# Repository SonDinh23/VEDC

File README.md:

# VEDC.dev

<div align="center">

<sub>
  Vedc v0.1 Front Top product (left), Front Bottom product (right)
</sub>

<sub>
  Vedc v0.1 Back Top product (left), Back Bottom product (right)
</sub>
</div>

## Table of contents

- [About](#about)
- [Platform snapshot](#platform-snapshot)
- [Features](#features)
  - [Hardware](#hardware)
  - [Firmware](#firmware)
  - [Software](#software)
- [Environment & build](#environment--build)
- [Writing apps for the Application Manager](#writing-apps-for-the-application-manager)
- [Licence GPL-3.0](#licence-gpl-30)
- [Thanks](#thanks)

## About

VEDC is a wearable biomedical reference design that blends EMG, ECG, and PPG sensing in a developer-friendly package. The hardware stack is fully captured in KiCad, the firmware targets ESP32-PICO-V3-02 via PlatformIO, and all production assets live in this repo so you can reproduce the build or remix it for your own research.

## Platform snapshot

| Item | Detail |
| --- | --- |
| MCU | ESP32-PICO-V3-02 (dual-core Xtensa®, Wi-Fi + BLE, 8 MB flash, 2 MB PSRAM) |
| Sensors | EMG analog front-end, ECG (AD8232), PPG module, 6-axis IMU, magnetometer |
| Connectivity | Wi-Fi 2.4 GHz, Bluetooth v4.2, USB-C (CP2102N), TWAI®/CAN-ready |
| Power | Single-cell Li-Ion + TP4056 charger + XC6220 LDO + smart power-path on MainPCB |
| Target use | Physiology research, medical wearables prototyping, advanced hobby builds |

### Core silicon & companion parts

- ESP32-PICO-V3-02 ([datasheet](https://documentation.espressif.com/esp32-pico_series_datasheet_en.pdf)) with Xtensa® LX6 up to 240 MHz, Wi-Fi/BLE, Ethernet MAC and TWAI®.
- Torex [XC6220B331MR-G](https://www.farnell.com/datasheets/2012852.pdf) 1 A, 3.3 V low-noise LDO for the digital rail.
- Silicon Labs [CP2102N-A02-GQFN28](https://www.silabs.com/documents/public/data-sheets/cp2102n-datasheet.pdf) USB-to-UART bridge for flashing, logging and live telemetry.
- Worldsemi [WS2812B-2020](https://www.mouser.com/pdfDocs/WS2812B-2020_V10_EN_181106150240761.pdf) RGB indicator, Murata [PKMCS0909E4000-R1](https://pim.murata.com/en-us/pim/details/?partNum=PKMCS0909E4000-R1) piezo buzzer, Microchip [MCP3204](https://ww1.microchip.com/downloads/en/devicedoc/21298e.pdf) SPI ADC.
- ST [LSM6DSL](https://www.st.com/resource/en/datasheet/lsm6dsl.pdf) IMU + [LIS3MDL](https://www.st.com/resource/en/datasheet/lis3mdl.pdf) magnetometer for motion/orientation tracking.
- Analog Devices [AD8232](https://www.analog.com/media/en/technical-documentation/data-sheets/ad8232.pdf) ECG AFE and a custom EMG front-end for bio-signal capture.
- TPASIC [TP4056](https://datasheet.lcsc.com/lcsc/1809261820_TOPPOWER-Nanjing-Extension-Microelectronics-TP4056-42-ESOP8_C16581.pdf) charger IC for USB-powered Li-Ion management.

## Features

### Hardware

- Three KiCad projects: EMGSensor, MainPCB, and PPG_V1.0. Each board section includes schematics, PCB layout, manufacturing outputs, notes, and galleries.
- Design focus on low-noise analog front-ends, modular interconnects, and easy probing during validation.
- Production-ready assets: BOM, pick-and-place, netlist, and positional data are stored under every `production/` folder.

[Browse board documentation →](hardware/README.md)

### Firmware

- ESP-IDF/PlatformIO stack targeting ESP32-PICO-V3-02 with FreeRTOS scheduling, NimBLE-based BLE services, USB-UART telemetry, and low-power modes.
- Sensor pipelines for EMG/ECG/PPG including digital filtering, adaptive baseline tracking, and event triggers for motion artifacts.
- Modular drivers housed under `firmware/Embedded/lib/` plus an application layer that streams metrics to BLE characteristics or logs via UART.
- Includes board bring-up helpers (rail monitors, sensor self-tests) and a configurable command shell.

[Read the full firmware guide →](firmware/README.md)

### Software

- Companion tooling (desktop/mobile) is planned to visualize BLE data streams, annotate sessions, and push OTA payloads.
- Current repo includes assets and API constraints so third parties can prototype dashboards or research tools ahead of the official release.
- Planned features: live waveform view, biomarker extraction scripts, and CSV export for MATLAB/Python workflows.

Have tooling to share? Open an issue so we can link it here.

## Environment & build

### Requirements

- VS Code with the PlatformIO IDE extension (or PlatformIO Core CLI).
- Python 3.10+ (PlatformIO manages the toolchain, but Python is still required).
- KiCad 7+ if you plan to edit the hardware.
- Git LFS for large media assets (images/live captures).

### Quick start

1. Clone the repo: `git clone https://github.com/SonDinh23/VEDC.git && cd VEDC`.
2. Open VS Code -> `firmware/` folder -> PlatformIO will auto-configure the environment.
3. Build: `pio run` (or the PlatformIO Build button).
4. Flash: connect the board over USB-C, then `pio run -t upload`.
5. Monitor logs: `pio device monitor` for UART output, or use the BLE explorer of your choice to view live characteristics.
6. Hardware tweaks: jump into `hardware/README.md` to pick the board you want to fabricate or review.

## Writing apps for the Application Manager

- The Application Manager exposes hooks for real-time sensing apps (recording, feedback) and offline routines (log replay, calibration).
- Apps are plain C++ modules that register tasks, BLE endpoints, and menu entries; use the existing patterns under `firmware/Embedded/src/` and supporting libraries in `firmware/Embedded/lib/` as templates.
- Keep apps lightweight: offload heavy analytics to the companion software via BLE or UART streaming.
- Submit a PR or discussion thread before merging new app types so we can document protocol additions for users.

## Licence GPL-3.0

This project is licensed under the GNU GPLv3.  
Compared to permissive licences like MIT, GPLv3 requires that if you modify this code and distribute your version (including in commercial products), you must also release your changes under the same GPLv3 licence and provide the corresponding source code.  

This way, everyone can benefit from improvements built on top of this project.  
If this licence causes issues for your intended use, feel free to contact me – I’m open to discussing alternatives.

## Thanks

Huge thanks to the open-source communities behind ESP-IDF, PlatformIO, KiCad, and the component vendors whose public documentation made reverse-engineering painless. Additional appreciation goes to early testers who provided waveform captures and enclosure feedback. Reach out if you want to be listed here or contribute design critiques.

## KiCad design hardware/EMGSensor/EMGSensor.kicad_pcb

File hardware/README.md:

# 🔧 Hardware Reference

Reference hub for every PCB in the VEDC stack. Each section collects the essential narrative (what the board does), quick specs, manufacturing artifacts, bring-up notes and a gallery that matches the files committed to this repo.

## 📌 At-a-glance

| Board | Functional role | Primary interfaces | Manufacturing kit |
| --- | --- | --- | --- |
| [EMGSensor](#emgsensor) | Surface EMG analog front-end with selectable filtering | Differential electrodes, analog output to MainPCB/ADC | `EMGSensor/*.kicad_*`, `EMGSensor/production/` |
| [MainPCB](#mainpcb) | System backplane: power, MCU, sensor connectors & user IO | USB-C, SPI, I2C, GPIO, battery charger, programming header | `MainPCB/*.kicad_*`, `MainPCB/production/` |
| [PPG_V1.0](#ppg_v10) | Optical heart-rate/SpO2 module (LED driver + TIA) | LED drive, photodiode TIA, analog output to MainPCB | `PPG_V1.0/*.kicad_*`, `PPG_V1.0/production/` |

---

## 🧠 EMGSensor

### Highlights
- Low-noise EMG front-end with band-pass filtering and input protection.
- Differential electrode inputs converted to a conditioned analog output for the main MCU/ADC.
- Designed to keep the analog ground plane quiet and isolated from digital switching noise.

### Quick specs

| Parameter | Detail |
| --- | --- |
| Signal type | Differential surface EMG |
| Input range | Microvolt → millivolt (depends on electrode placement) |
| Bandwidth | Application-configurable band-pass |
| Output | Analog to `MainPCB` or external ADC |

### Manufacturing files
- `EMGSensor/EMGSensor.kicad_sch`
- `EMGSensor/EMGSensor.kicad_pcb`
- `EMGSensor/production/` (BOM, placements, netlist, positions)

### Build & test checklist
- Keep electrode traces short/shielded and preserve the analog ground island.
- Verify input protection and supply rails before connecting electrodes to humans.
- Adjust filter corners so they align with sampling rate and targeted muscle group.

### Gallery

<table>
  <tr>
    <td align="center"><br><small>Top — module overview</small></td>
    <td align="center"><br><small>Top — amplifier/filter</small></td>
    <td align="center"><br><small>Top — connectors</small></td>
  </tr>
  <tr>
    <td align="center"><br><small>Bottom — solder side</small></td>
    <td align="center"><br><small>Bottom — ground pours</small></td>
    <td align="center"><br><small>Bottom — component placement</small></td>
  </tr>
</table>

---

## 🧭 MainPCB

### Highlights
- Primary compute board with ESP32 module, battery charging/power-path management and sensor interconnects.
- Hosts debug/programming headers, USB-UART bridge, IMU/ADC expansion headers and NeoPixel/buzzer drivers.
- Provides regulated rails (3V3 etc.) and mounting keep-outs for future enclosures.

### Quick specs

| Parameter | Detail |
| --- | --- |
| Core function | Power distribution + embedded processing |
| Key rails | Battery, charger IC, 3V3 LDO, load switches |
| Interfaces | USB/serial, SPI, I2C, ADC, GPIO, programming header |

### Manufacturing files
- `MainPCB/MainPCB.kicad_sch`
- `MainPCB/MainPCB.kicad_pcb`
- `MainPCB/production/` (BOM, placements, netlist, positions)

### Build & test checklist
- Cross-check BOM vs placement before assembly to avoid variant mix-ups.
- Validate mechanical clearances/keep-outs when fitting into an enclosure.
- Probe test points for each rail during bring-up; confirm charger and LDO thermals.

### Gallery

<table>
  <tr>
    <td align="center"><br><small>Top — overview</small></td>
    <td align="center"><br><small>Top — MCU & IO</small></td>
    <td align="center"><br><small>Top — power subsystem</small></td>
  </tr>
  <tr>
    <td align="center"><br><small>Bottom — solder side</small></td>
    <td align="center"><br><small>Bottom — pours & routing</small></td>
    <td align="center"><br><small>Bottom — placement</small></td>
  </tr>
</table>

---

## 💡 PPG_V1.0

### Highlights
- Dual-LED photoplethysmography front-end with transimpedance amplifier.
- Layout keeps LED/photodiode path compact to reduce crosstalk and improve tissue coupling.
- Analog output routes directly to MainPCB analog inputs or an external ADC.

### Quick specs

| Parameter | Detail |
| --- | --- |
| Role | Optical heart-rate / blood-volume sensing |
| Key blocks | LED driver, photodetector + TIA, post-filtering |
| Output | Analog to `MainPCB` / ADC |

### Manufacturing files
- `PPG_V1.0/PPG_V1.0.kicad_sch`
- `PPG_V1.0/PPG_V1.0.kicad_pcb`
- `PPG_V1.0/production/` (BOM, placements, netlist, positions)

### Build & test checklist
- Align LEDs and photodiode carefully; even small misalignments affect signal quality.
- Tune LED current and TIA feedback for the target SNR vs power budget.
- Shield the sensor head from ambient light during characterization.

### Gallery

<table>
  <tr>
    <td align="center"><br><small>Top — overview</small></td>
    <td align="center"><br><small>Top — LED/receiver zone</small></td>
  </tr>
  <tr>
    <td align="center"><br><small>Bottom — solder side</small></td>
    <td align="center"><br><small>Bottom — placement view</small></td>
  </tr>
</table>

---

## 🖼️ Image & path guidance

- Use forward slashes `/` in Markdown image paths; all current links are relative to this README.
- Example snippet: ``.
- GitHub renders images only after the corresponding PNG/SVG files are committed and pushed.
- Need a different layout (per-board README, thumbnail sizes, PDF gallery)? Let me know and I can spin up that structure quickly.

---

_Last refreshed: see git history for author/date of the latest board update._

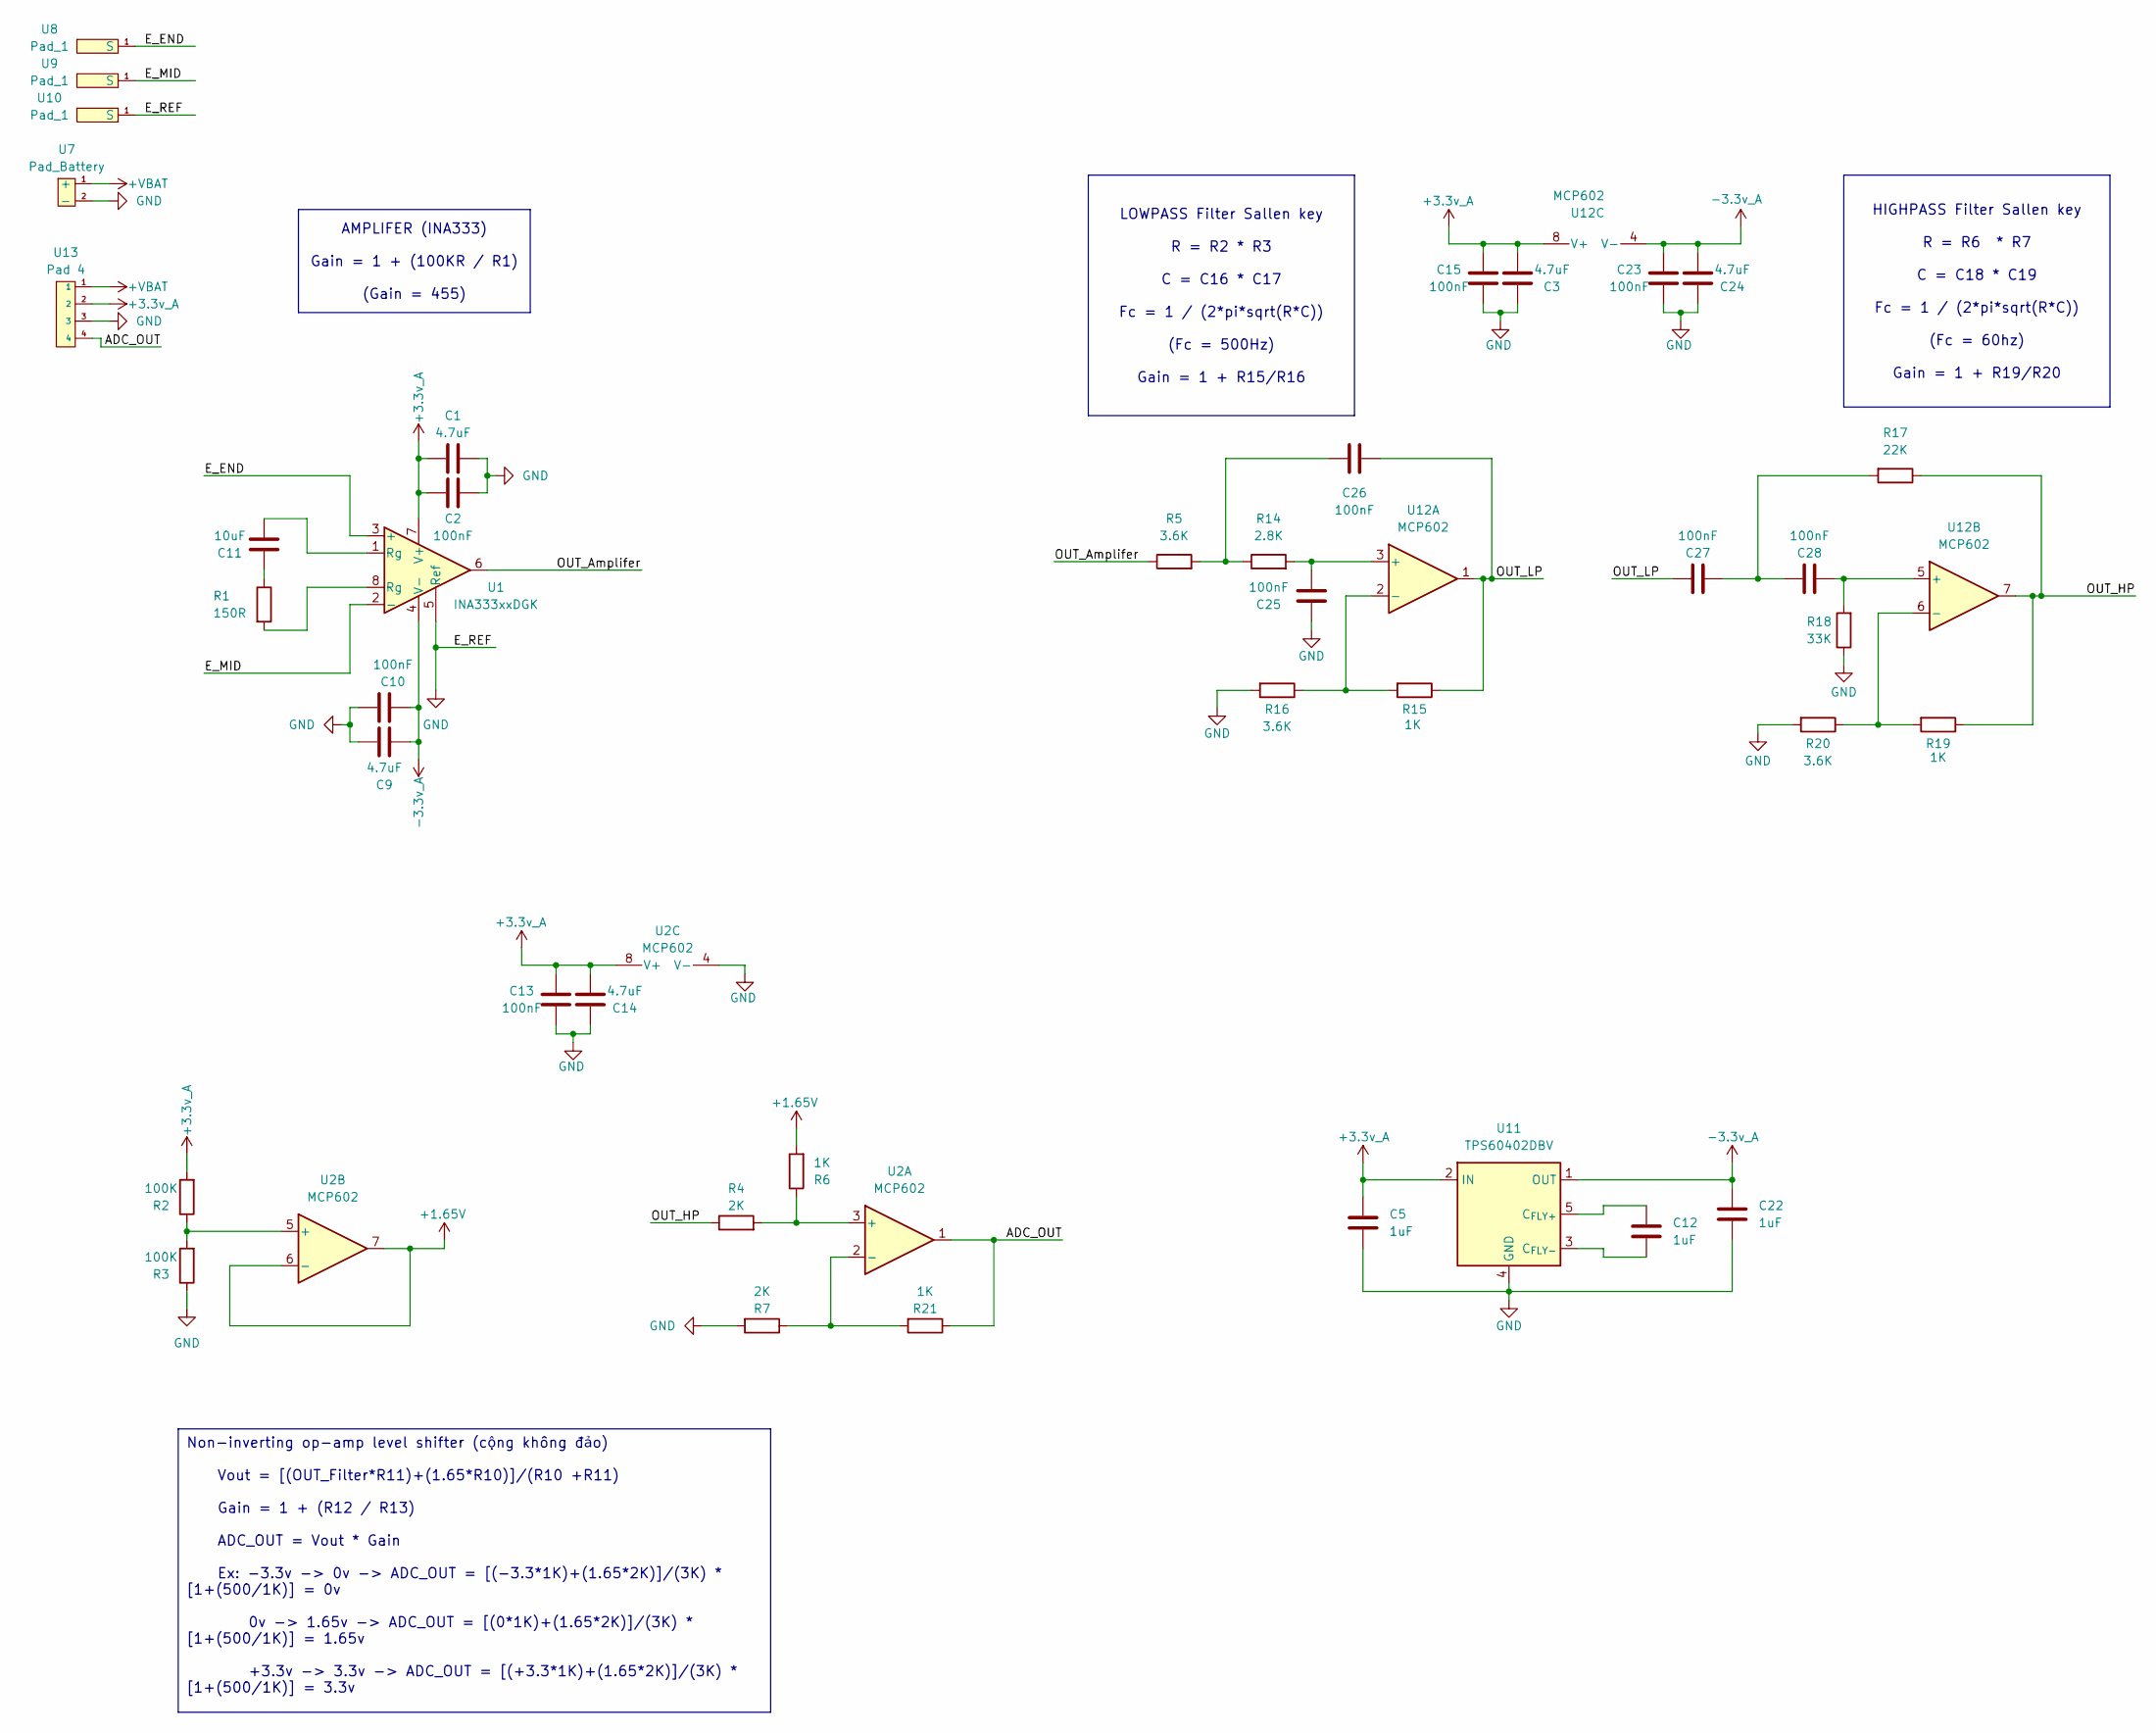
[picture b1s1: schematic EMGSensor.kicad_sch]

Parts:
C1, C3, C9, C14, C24: 4.7uF; C_0402_1005Metric
C2, C10, C13, C15, C23, C25, C26, C27, C28: 100nF; C_0402_1005Metric
C5, C12, C22: 1uF; C_0402_1005Metric
C11: 10uF; C_0603_1608Metric
R1: 150R; R_0402_1005Metric
R2, R3: 100K; R_0402_1005Metric
R4, R7: 2K; R_0402_1005Metric
R5, R16, R20: 3.6K; R_0402_1005Metric
R6, R15, R19, R21: 1K; R_0402_1005Metric
R14: 2.8K; R_0402_1005Metric
R17: 22K; R_0402_1005Metric
R18: 33K; R_0402_1005Metric
U1: INA333xxDGK; VSSOP-8_3x3mm_P0.65mm
U2, U12: MCP602; SOIC-8_3.9x4.9mm_P1.27mm
U7: Pad_Battery; Pad Battery
U8, U9, U10: Pad_1; Pad 1
U11: TPS60402DBV; SOT-23-5
U13: Pad 4

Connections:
+1.65V: R6.2, U2.6 (-), U2.7
+3.3v_A: C1.1, C2.1, C3.1, C5.1, C13.1, C14.1, C15.1, R2.2, U1.7 (V+), U2.8 (V+), U11.2 (IN), U12.8 (V+), U13.2
+VBAT: U7.1 (+), U13.1
-3.3v_A: C9.1, C10.1, C22.1, C23.1, C24.1, U1.4 (V-), U11.1 (OUT), U12.4 (V-)
/ADC_OUT: R21.1, U2.1, U13.4
/E_END: U1.3 (+), U8.1
/E_MID: U1.2 (-), U9.1
/OUT_Amplifer: R5.1, U1.6
/OUT_HP: R4.1, R17.1, R19.1, U12.7
/OUT_LP: C26.1, C27.2, R15.1, U12.1
GND: C1.2, C2.2, C3.2, C5.2, C9.2, C10.2, C13.2, C14.2, C15.2, C22.2, C23.2, C24.2, C25.1, R3.1, R7.2, R16.2, R18.1, R20.2, U1.5 (Ref), U2.4 (V-), U7.2 (-), U10.1 (S), U11.4 (GND), U13.3
unnamed: C11.1, R1.1
unnamed: C11.2, U1.1 (Rg)
unnamed: C26.2, R5.2, R14.1
unnamed: C27.1, C28.2, R17.2
unnamed: R1.2, U1.8 (Rg)
unnamed: R4.2, R6.1, U2.3 (+)
unnamed: R7.1, R21.2, U2.2 (-)
unnamed: R2.1, R3.2, U2.5 (+)
unnamed: C12.1, U11.5 (C_{FLY+})
unnamed: C12.2, U11.3 (C_{FLY-})
unnamed: C25.2, R14.2, U12.3 (+)
unnamed: R15.2, R16.1, U12.2 (-)
unnamed: C28.1, R18.2, U12.5 (+)
unnamed: R19.2, R20.1, U12.6 (-)

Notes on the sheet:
Non-inverting op-amp level shifter (cộng không đảo) Vout = [(OUT_Filter*R11)+(1.65*R10)]/(R10 +R11) Gain = 1 + (R12 / R13) ADC_OUT = Vout * Gain Ex: -3.3v -> 0v -> ADC_OUT = [(-3.3*1K)+(1.65*2K)]/(3K) * [1+(500/1K)] = 0v 0v -> 1.65v -> ADC_OUT = [(0*1K)+(1.65*2K)]/(3K) * [1+(500/1K)] = 1.65v +3.3v 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
LOWPASS Filter Sallen key R = R2 * R3 C = C16 * C17 Fc = 1 / (2*pi*sqrt(R*C)) (Fc = 500Hz) Gain = 1 + R15/R16
AMPLIFER (INA333) Gain = 1 + (100KR / R1) (Gain = 455)
HIGHPASS Filter Sallen key R = R6 * R7 C = C18 * C19 Fc = 1 / (2*pi*sqrt(R*C)) (Fc = 60hz) Gain = 1 + R19/R20

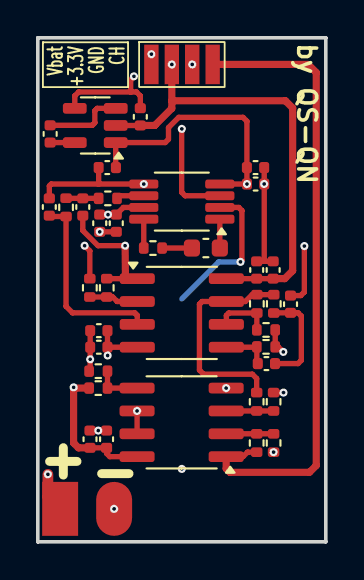
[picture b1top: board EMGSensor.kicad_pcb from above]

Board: 4 copper layers, 16.0 x 28.0 mm, 40 parts (0 on the bottom side), 23 nets.

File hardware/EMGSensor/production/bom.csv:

Designator,Footprint,Quantity,Value,LCSC Part #
"_2, ",,2,,
"C1, C14, C24, C3, C9",0402,5,4.7uF,
"C10, C13, C15, C2, C23, C25, C26, C27, C28",0402,9,100nF,
C11,0603,1,10uF,
"C12, C22, C5",0402,3,1uF,
R1,0402,1,220R,
R14,0402,1,2.8K,
"R15, R19, R21, R6",0402,4,1K,
"R16, R20, R5",0402,3,3.6K,
R17,0402,1,22K,
R18,0402,1,33K,
"R2, R3",0402,2,100K,
"R4, R7",0402,2,2K,
U1,VSSOP-8_3x3mm_P0.65mm,1,INA333xxDGK,
U10,Pad 1,1,Pad,
U11,SOT-23-5,1,TPS60402DBV,
"U12, U2",SOIC-8_3.9x4.9mm_P1.27mm,2,MCP602,
U13,Pad 4,1,Pad 4,
U7,Pad Battery,1,Pad_Battery,

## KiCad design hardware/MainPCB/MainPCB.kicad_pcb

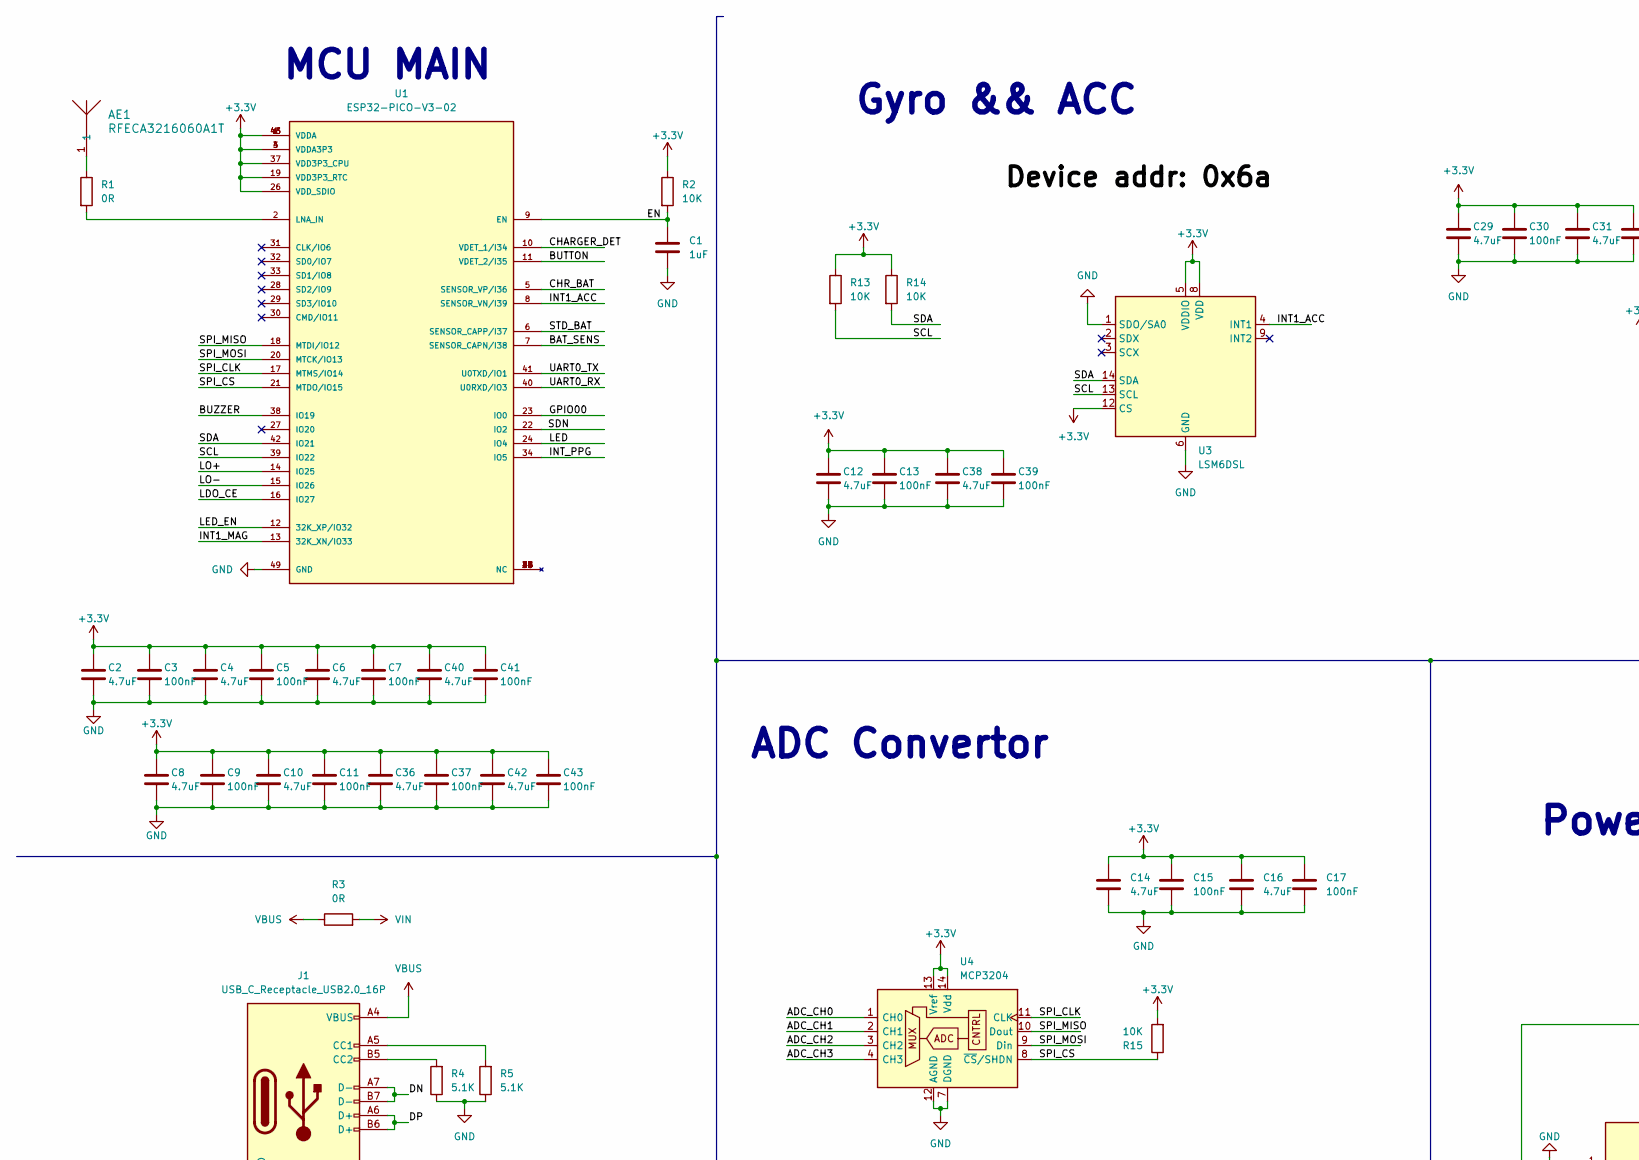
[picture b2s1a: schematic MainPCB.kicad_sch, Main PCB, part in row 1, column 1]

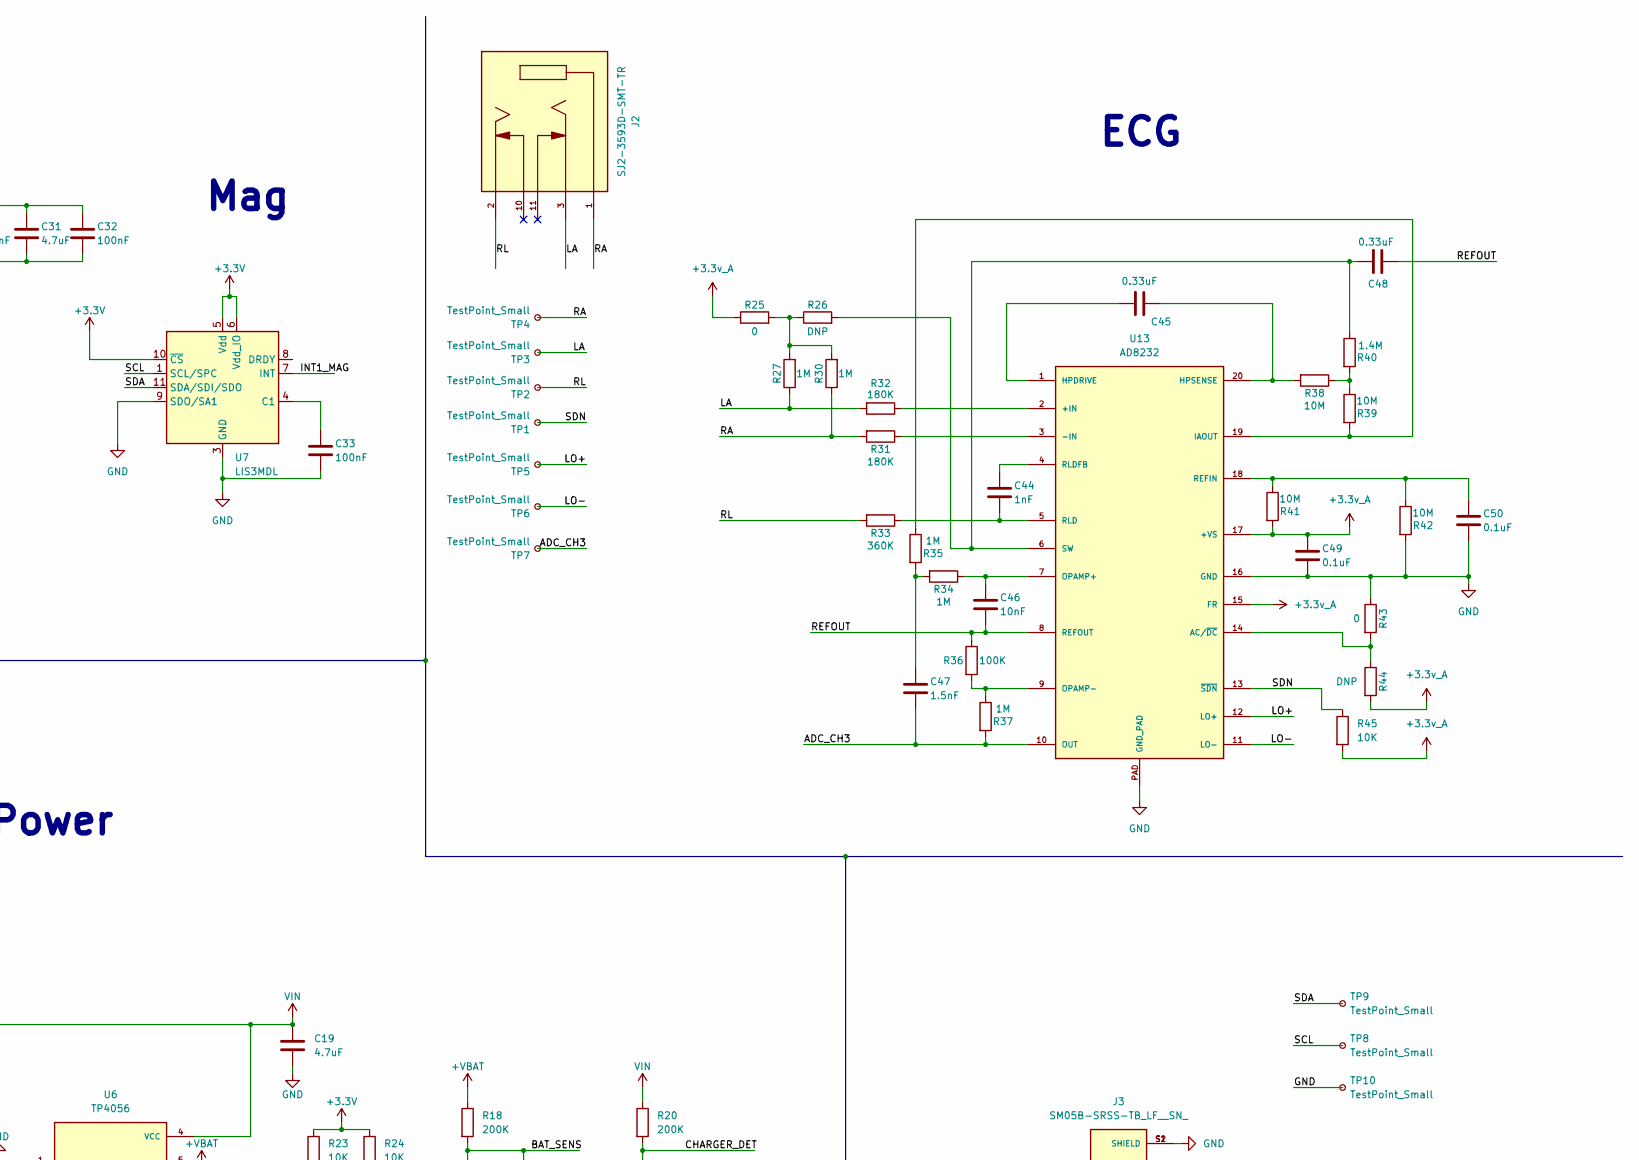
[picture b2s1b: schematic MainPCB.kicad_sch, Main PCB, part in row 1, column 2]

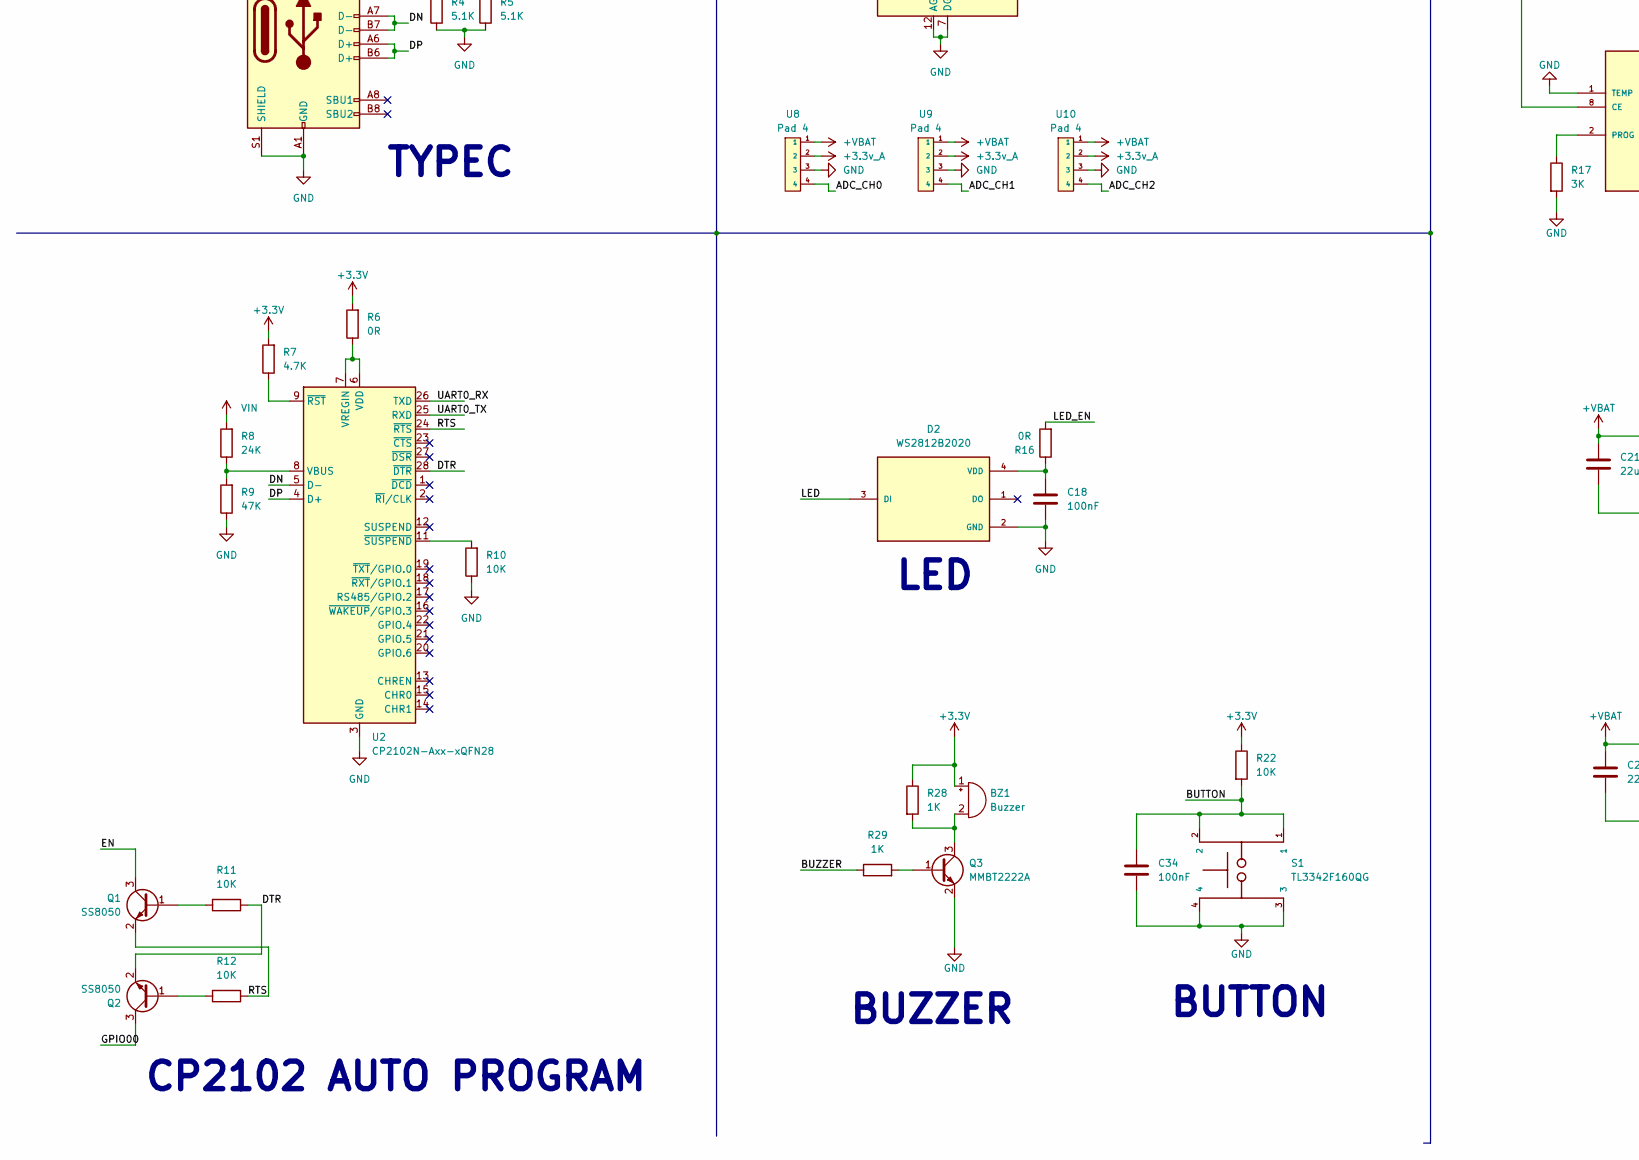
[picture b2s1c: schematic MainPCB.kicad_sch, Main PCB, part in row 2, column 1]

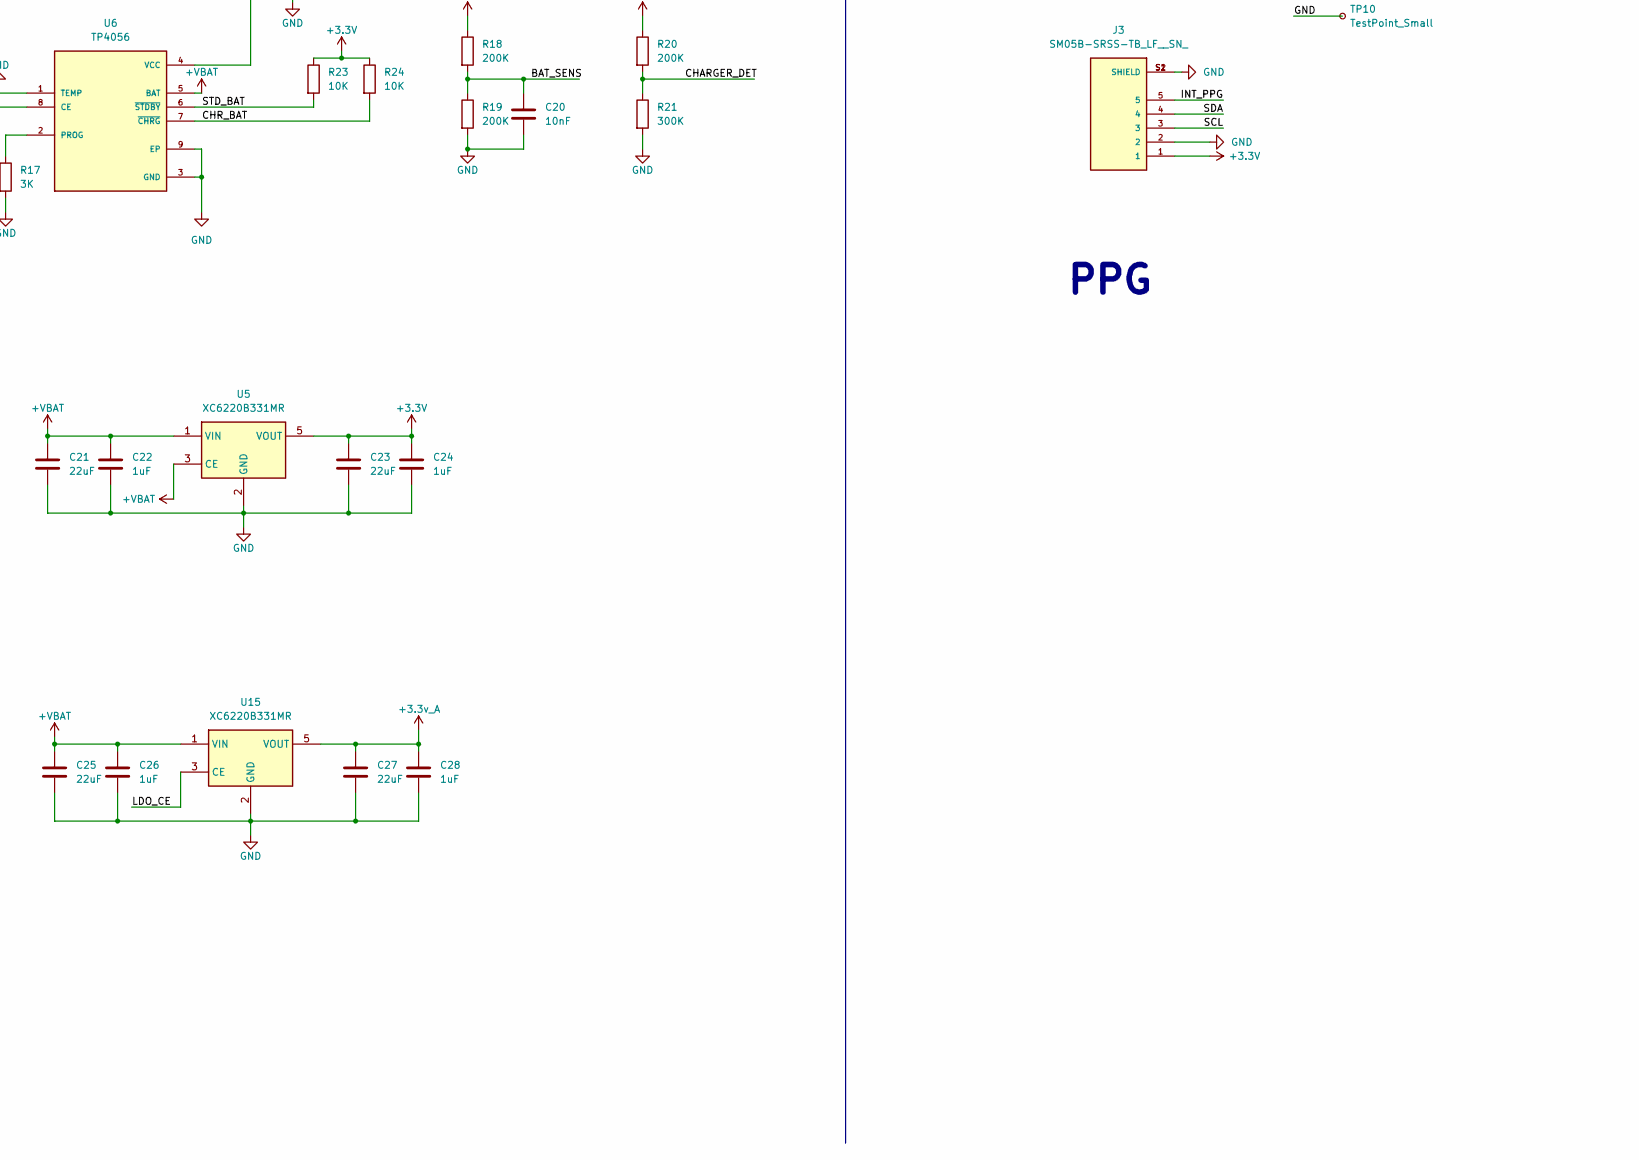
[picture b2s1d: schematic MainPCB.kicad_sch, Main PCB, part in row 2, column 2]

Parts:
AE1: RFECA3216060A1T; ANT_16060A1T_WAL
BZ1: Buzzer; Buzzer_Murata_PKMCS0909E
C1, C22, C24, C26, C28: 1uF; C_0402_1005Metric
C2, C4, C6, C8, C10, C12, C14, C16, C19, C29, C31, C36, C38, C40, C42: 4.7uF; C_0402_1005Metric
C3, C5, C7, C9, C11, C13, C15, C17, C18, C30, C32, C33, C34, C37, C39, C41, C43: 100nF; C_0402_1005Metric
C20, C46: 10nF; C_0402_1005Metric
C21, C23, C25, C27: 22uF; C_0603_1608Metric
C44: 1nF; C_0402_1005Metric
C45, C48: 0.33uF; C_0402_1005Metric
C47: 1.5nF; C_0402_1005Metric
C49, C50: 0.1uF; C_0402_1005Metric
D2: WS2812B2020; LED_WS2812B2020; PARTREV V1.0
J1: USB_C_Receptacle_USB2.0_16P; USB_C_Receptacle_GCT_USB4105-xx-A_16P_TopMnt_Horizontal
J2: SJ2-3593D-SMT-TR; CUI_SJ2-3593D-SMT-TR; PARTREV 1.04
J3: SM05B-SRSS-TB_LF__SN_; JST_SM05B-SRSS-TB_LF__SN_
Q1, Q2: SS8050; SOT-23
Q3: MMBT2222A; SOT-23
R1, R3, R6, R16: 0R; C_0402_1005Metric
R2, R10, R11, R12, R13, R14, R15, R22, R23, R24, R45: 10K; C_0402_1005Metric
R4, R5: 5.1K; C_0402_1005Metric
R7: 4.7K; C_0402_1005Metric
R8: 24K; C_0402_1005Metric
R9: 47K; C_0402_1005Metric
R17: 3K; C_0402_1005Metric
R18, R19, R20: 200K; C_0402_1005Metric
R21: 300K; C_0402_1005Metric
R25, R43: 0; C_0402_1005Metric
R26, R44: DNP; C_0402_1005Metric
R27, R30, R34, R35, R37: 1M; C_0402_1005Metric
R28, R29: 1K; C_0402_1005Metric
R31, R32: 180K; C_0402_1005Metric
R33: 360K; C_0402_1005Metric
R36: 100K; C_0402_1005Metric
R38, R39, R41, R42: 10M; C_0402_1005Metric
R40: 1.4M; C_0402_1005Metric
S1: TL3342F160QG; SW_TL3342F160QG
TP1, TP2, TP3, TP4, TP5, TP6, TP7, TP8, TP9, TP10: TestPoint_Small; TestPoint_Pad_D1.0mm
U1: ESP32-PICO-V3-02; XCVR_ESP32-PICO-V3-02; PARTREV 1.0
U2: CP2102N-Axx-xQFN28; QFN-28-1EP_5x5mm_P0.5mm_EP3.35x3.35mm
U3: LSM6DSL; LGA-14_3x2.5mm_P0.5mm_LayoutBorder3x4y
U4: MCP3204; TSSOP-14_4.4x5mm_P0.65mm
U5, U15: XC6220B331MR; SOT-23-5
U6: TP4056; SOP127P600X175-9N
U7: LIS3MDL; LGA-12_2x2mm_P0.5mm
U8, U9, U10: Pad 4
U13: AD8232; LFCSP_20

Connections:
+3.3V: BZ1.1 (+), C2.1, C3.1, C4.1, C5.1, C6.1, C7.1, C8.1, C9.1, C10.1, C11.1, C12.1, C13.1, C14.1, C15.1, C16.1, C17.1, C23.1, C24.1, C29.1, C30.1, C31.1, C32.1, C36.1, C37.1, C38.1, C39.1, C40.1, C41.1, C42.1, C43.1, J3.1, R2.1, R6.2, R7.2, R13.1, R14.1, R15.2, R22.1, R23.1, R24.1, R28.1, U1.1 (VDDA), U1.3 (VDDA3P3), U1.4 (VDDA3P3), U1.19 (VDD3P3_RTC), U1.26 (VDD_SDIO), U1.37 (VDD3P3_CPU), U1.43 (VDDA), U1.46 (VDDA), U3.5 (VDDIO), U3.8 (VDD), U3.12 (CS), U4.13 (Vref), U4.14 (Vdd), U5.5 (VOUT), U7.5 (Vdd), U7.6 (Vdd_IO), U7.10 (~CS)
+3.3v_A: C27.1, C28.1, C49.1, R25.1, R41.2, R44.2, R45.2, U8.2, U9.2, U10.2, U13.15 (FR), U13.17 (+VS), U15.5 (VOUT)
+VBAT: C21.1, C22.1, C25.1, C26.1, R18.1, U5.1 (VIN), U5.3 (CE), U6.5 (BAT), U8.1, U9.1, U10.1, U15.1 (VIN)
/ADC_CH0: U4.1 (CH0), U8.4
/ADC_CH1: U4.2 (CH1), U9.4
/ADC_CH2: U4.3 (CH2), U10.4
/ADC_CH3: C47.2, R37.2, TP7.1, U4.4 (CH3), U13.10 (OUT)
/BAT_SENS: C20.1, R18.2, R19.1, U1.7 (SENSOR_CAPN/I38)
/BUTTON: C34.1, R22.2, S1.1, S1.2, U1.11 (VDET_2/I35)
/BUZZER: R29.1, U1.38 (IO19)
/CHARGER_DET: R20.2, R21.1, U1.10 (VDET_1/I34)
/CHR_BAT: R24.2, U1.5 (SENSOR_VP/I36), U6.7 (~CHRG)
/DN: J1.A7 (D-), J1.B7 (D-), U2.5 (D-)
/DP: J1.A6 (D+), J1.B6 (D+), U2.4 (D+)
/DTR: Q2.2 (E), R11.1, U2.28 (~DTR)
/EN: C1.1, Q1.3 (C), R2.2, U1.9 (EN)
/GPIO00: Q2.3 (C), U1.23 (IO0)
/INT1_ACC: U1.8 (SENSOR_VN/I39), U3.4 (INT1)
/INT1_MAG: U1.13 (32K_XN/IO33), U7.7 (INT)
/INT_PPG: J3.5, U1.34 (IO5)
/LA: J2.3, R27.1, R32.2, TP3.1
/LDO_CE: U1.16 (IO27), U15.3 (CE)
/LED: D2.3 (DI), U1.24 (IO4)
/LED_EN: R16.2, U1.12 (32K_XP/IO32)
/LO+: TP5.1, U1.14 (IO25), U13.12 (LO+)
/LO-: TP6.1, U1.15 (IO26), U13.11 (LO-)
/RA: J2.1, R30.1, R31.2, TP4.1
/REFOUT: C46.2, C48.2, R36.1, U13.8 (REFOUT)
/RL: J2.2, R33.2, TP2.1
/RTS: Q1.2 (E), R12.1, U2.24 (~RTS)
/SCL: J3.3, R13.2, TP8.1, U1.39 (IO22), U3.13 (SCL), U7.1 (SCL/SPC)
/SDA: J3.4, R14.2, TP9.1, U1.42 (IO21), U3.14 (SDA), U7.11 (SDA/SDI/SDO)
/SDN: R45.1, TP1.1, U1.22 (IO2), U13.13 (~SDN)
/SPI_CLK: U1.17 (MTMS/IO14), U4.11 (CLK)
/SPI_CS: R15.1, U1.21 (MTDO/IO15), U4.8 (~CS/SHDN)
/SPI_MISO: U1.18 (MTDI/IO12), U4.10 (Dout)
/SPI_MOSI: U1.20 (MTCK/IO13), U4.9 (Din)
/STD_BAT: R23.2, U1.6 (SENSOR_CAPP/I37), U6.6 (~STDBY)
/UART0_RX: U1.40 (U0RXD/IO3), U2.26 (TXD)
/UART0_TX: U1.41 (U0TXD/IO1), U2.25 (RXD)
GND: C1.2, C2.2, C3.2, C4.2, C5.2, C6.2, C7.2, C8.2, C9.2, C10.2, C11.2, C12.2, C13.2, C14.2, C15.2, C16.2, C17.2, C18.2, C19.2, C20.2, C21.2, C22.2, C23.2, C24.2, C25.2, C26.2, C27.2, C28.2, C29.2, C30.2, C31.2, C32.2, C33.2, C34.2, C36.2, C37.2, C38.2, C39.2, C40.2, C41.2, C42.2, C43.2, C49.2, C50.2, D2.2 (GND), J1.A1 (GND), J1.A12 (GND), J1.B1 (GND), J1.B12 (GND), J1.S1 (SHIELD), J3.2, J3.S1 (SHIELD), J3.S2 (SHIELD), Q3.2 (E), R4.1, R5.1, R9.1, R10.1, R17.2, R19.2, R21.2, R42.2, R43.1, S1.3, S1.4, TP10.1, U1.49 (GND), U2.3 (GND), U2.29 (GND), U3.1 (SDO/SA0), U3.6 (GND), U3.7 (GND), U4.7 (DGND), U4.12 (AGND), U5.2 (GND), U6.1 (TEMP), U6.3 (GND), U6.9 (EP), U7.2 (GND), U7.3 (GND), U7.9 (SDO/SA1), U7.12 (GND), U8.3, U9.3, U10.3, U13.16 (GND), U13.PAD (GND_PAD), U15.2 (GND)
unnamed: AE1.1, R1.1
unnamed: BZ1.2 (-), Q3.3 (C), R28.2
unnamed: C47.1, R34.2, R35.2
unnamed: C18.1, D2.4 (VDD), R16.1
unnamed: J1.A5 (CC1), R5.2
unnamed: J1.B5 (CC2), R4.2
unnamed: Q1.1 (B), R11.2
unnamed: Q2.1 (B), R12.2
unnamed: Q3.1 (B), R29.2
unnamed: R25.2, R26.1, R27.2, R30.2
unnamed: R38.1, R39.1, R40.2
unnamed: R1.2, U1.2 (LNA_IN)
unnamed: R8.1, R9.2, U2.8 (VBUS)
unnamed: R6.1, U2.6 (VDD), U2.7 (VREGIN)
unnamed: R7.1, U2.9 (~RST)
unnamed: R10.2, U2.11 (~SUSPEND)
unnamed: R17.1, U6.2 (PROG)
unnamed: C33.1, U7.4 (C1)
unnamed: R32.1, U13.2 (+IN)
unnamed: R31.1, U13.3 (-IN)
unnamed: R43.2, R44.1, U13.14 (AC/~DC)
unnamed: C45.1, U13.1 (HPDRIVE)
unnamed: C45.2, R38.2, U13.20 (HPSENSE)
unnamed: R35.1, R39.2, U13.19 (IAOUT)
unnamed: C46.1, R34.1, U13.7 (OPAMP+)
unnamed: R36.2, R37.1, U13.9 (OPAMP-)
unnamed: C50.1, R41.1, R42.1, U13.18 (REFIN)
unnamed: C44.2, R33.1, U13.5 (RLD)
unnamed: C44.1, U13.4 (RLDFB)
unnamed: C48.1, R26.2, R40.1, U13.6 (SW)
VBUS: J1.A4 (VBUS), J1.A9 (VBUS), J1.B4 (VBUS), J1.B9 (VBUS), R3.1
VIN: C19.1, R3.2, R8.2, R20.1, U6.4 (VCC), U6.8 (CE)

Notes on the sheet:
PPG
LED
BUZZER
ADC Convertor
Power
Gyro && ACC
CP2102 AUTO PROGRAM
Mag
TYPEC
ECG
BUTTON
MCU MAIN

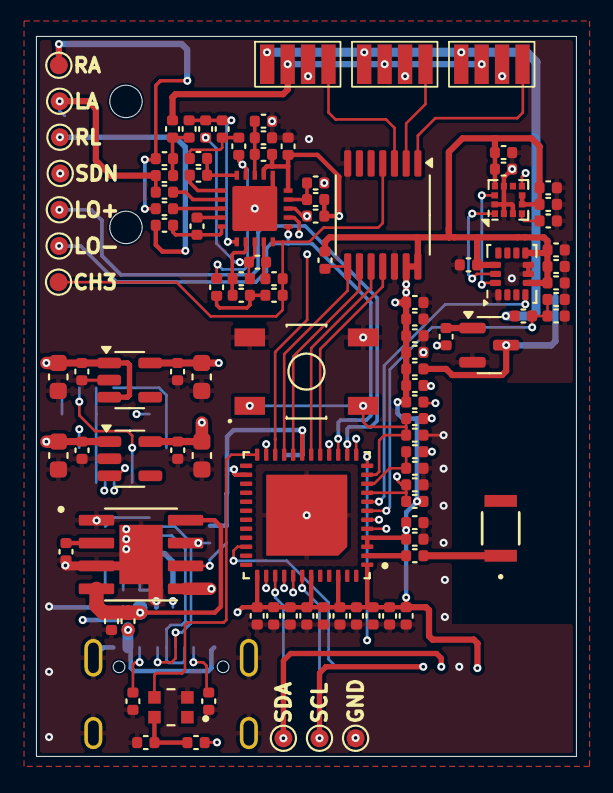
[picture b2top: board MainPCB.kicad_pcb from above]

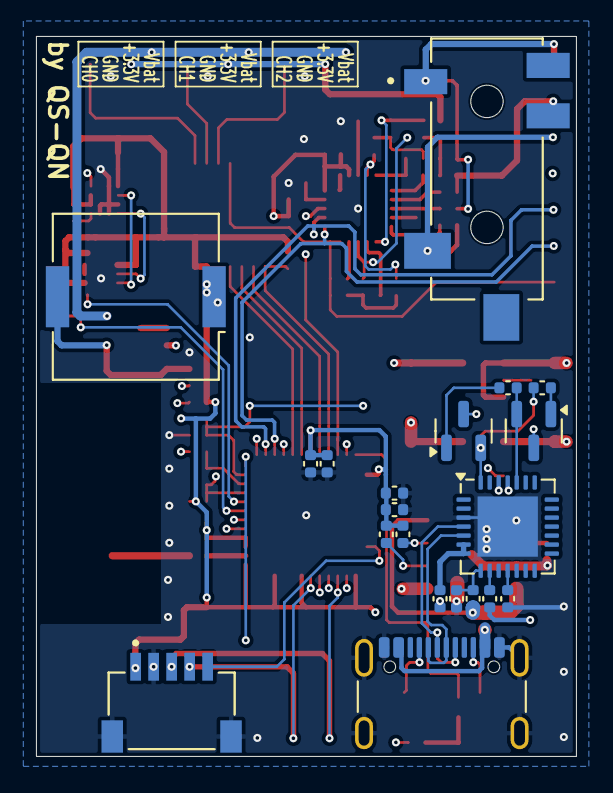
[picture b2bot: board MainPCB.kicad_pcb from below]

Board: 4 copper layers, 30.0 x 40.0 mm, 126 parts (20 on the bottom side), 73 nets.

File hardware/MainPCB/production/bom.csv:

Designator,Footprint,Quantity,Value,LCSC Part #
AE1,ANT_16060A1T_WAL,1,RFECA3216060A1T,
BZ1,Buzzer_Murata_PKMCS0909E,1,Buzzer,
"C1, C22, C24, C26, C28",0402,5,1uF,
"C10, C12, C14, C16, C19, C2, C29, C31, C36, C38, C4, C40, C42, C6, C8",0402,15,4.7uF,
"C11, C13, C15, C17, C18, C3, C30, C32, C33, C34, C37, C39, C41, C43, C5, C7, C9",0402,17,100nF,
"C20, C46",0402,2,10nF,
"C21, C23, C25, C27",0603,4,22uF,
C44,0402,1,1nF,
"C45, C48",0402,2,0.33uF,
C47,0402,1,1.5nF,
"C49, C50",0402,2,0.1uF,
D2,LED_WS2812B2020,1,WS2812B2020,
J1,USB_C_Receptacle_GCT_USB4105-xx-A_16P_TopMnt_Horizontal,1,USB_C_Receptacle_USB2.0_16P,
J2,CUI_SJ2-3593D-SMT-TR,1,SJ2-3593D-SMT-TR,
J3,JST_SM05B-SRSS-TB_LF__SN_,1,SM05B-SRSS-TB_LF__SN_,
"Q1, Q2",SOT-23,2,SS8050,
Q3,SOT-23,1,MMBT2222A,
"R1, R16, R3, R6",0402,4,0R,
"R10, R11, R12, R13, R14, R15, R2, R22, R23, R24, R45",0402,11,10K,
R17,0402,1,3K,
"R18, R19, R20",0402,3,200K,
R21,0402,1,300K,
"R25, R43",0402,2,0,
"R26, R44",0402,2,DNP,
"R27, R30, R34, R35, R37",0402,5,1M,
"R28, R29",0402,2,1K,
"R31, R32",0402,2,180K,
R33,0402,1,360K,
R36,0402,1,100K,
"R38, R39, R41, R42",0402,4,10M,
"R4, R5",0402,2,5.1K,
R40,0402,1,1.4M,
R7,0402,1,4.7K,
R8,0402,1,24K,
R9,0402,1,47K,
S1,SW_TL3342F160QG,1,TL3342F160QG,
"TP1, TP10, TP2, TP3, TP4, TP5, TP6, TP7, TP8, TP9",TestPoint_Pad_D1.0mm,10,TestPoint_Small,
U1,XCVR_ESP32-PICO-V3-02,1,ESP32-PICO-V3-02,
"U10, U8, U9",Pad 4,3,Pad 4,
U13,LFCSP_20,1,AD8232,
"U15, U5",SOT-23-5,2,XC6220B331MR,
U2,QFN-28-1EP_5x5mm_P0.5mm_EP3.35x3.35mm,1,CP2102N-Axx-xQFN28,
U3,LGA-14_3x2.5mm_P0.5mm_LayoutBorder3x4y,1,LSM6DSL,
U4,TSSOP-14_4.4x5mm_P0.65mm,1,MCP3204,
U6,SOP127P600X175-9N,1,TP4056,
U7,LGA-12_2x2mm_P0.5mm,1,LIS3MDL,

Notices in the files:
README.md:
License: GPL 3.0
